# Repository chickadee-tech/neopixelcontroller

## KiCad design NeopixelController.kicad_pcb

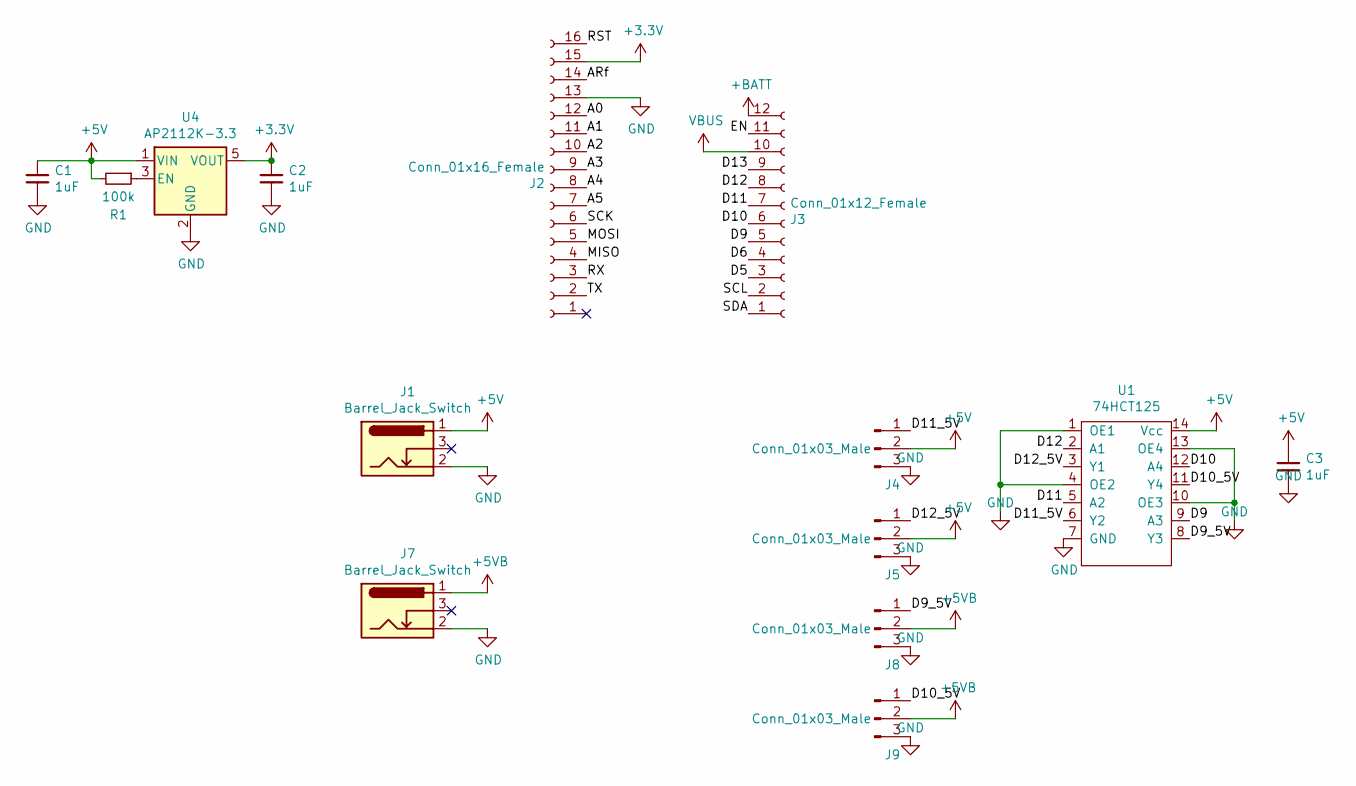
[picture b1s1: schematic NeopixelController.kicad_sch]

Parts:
C1, C2, C3: 1uF; C_0603_1608Metric_Pad1.05x0.95mm_HandSolder
J1, J7: Barrel_Jack_Switch; BarrelJack_CUI_PJ-102AH_Horizontal
J2: Conn_01x16_Female; PinSocket_1x16_P2.54mm_Vertical
J3: Conn_01x12_Female; PinSocket_1x12_P2.54mm_Vertical
J4, J5, J8, J9: Conn_01x03_Male; JST_PH_S3B-PH-K_1x03_P2.00mm_Horizontal
R1: 100k; R_0603_1608Metric_Pad1.05x0.95mm_HandSolder
U1: 74HCT125; TSSOP-14_4.4x5mm_P0.65mm
U4: AP2112K-3.3; SOT-23-5

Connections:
+3.3V: C2.1, J2.15, U4.5 (VOUT)
+5V: C1.1, C3.1, J1.1, J4.2, J5.2, R1.2, U1.14 (Vcc), U4.1 (VIN)
+5VB: J7.1, J8.2, J9.2
+BATT: J3.12
/A0: J2.12
/A1: J2.11
/A2: J2.10
/A3: J2.9
/A4: J2.8
/A5: J2.7
/ARf: J2.14
/D5: J3.3
/D6: J3.4
/D9: J3.5, U1.9 (A3)
/D9_5V: J8.1, U1.8 (Y3)
/D10: J3.6, U1.12 (A4)
/D10_5V: J9.1, U1.11 (Y4)
/D11: J3.7, U1.5 (A2)
/D11_5V: J4.1, U1.6 (Y2)
/D12: J3.8, U1.2 (A1)
/D12_5V: J5.1, U1.3 (Y1)
/D13: J3.9
/EN: J3.11
/MISO: J2.4
/MOSI: J2.5
/RST: J2.16
/RX: J2.3
/SCK: J2.6
/SCL: J3.2
/SDA: J3.1
/TX: J2.2
GND: C1.2, C2.2, C3.2, J1.2, J2.13, J4.3, J5.3, J7.2, J8.3, J9.3, U1.1 (OE1), U1.4 (OE2), U1.7 (GND), U1.10 (OE3), U1.13 (OE4), U4.2 (GND)
unnamed: R1.1, U4.3 (EN)
VBUS: J3.10

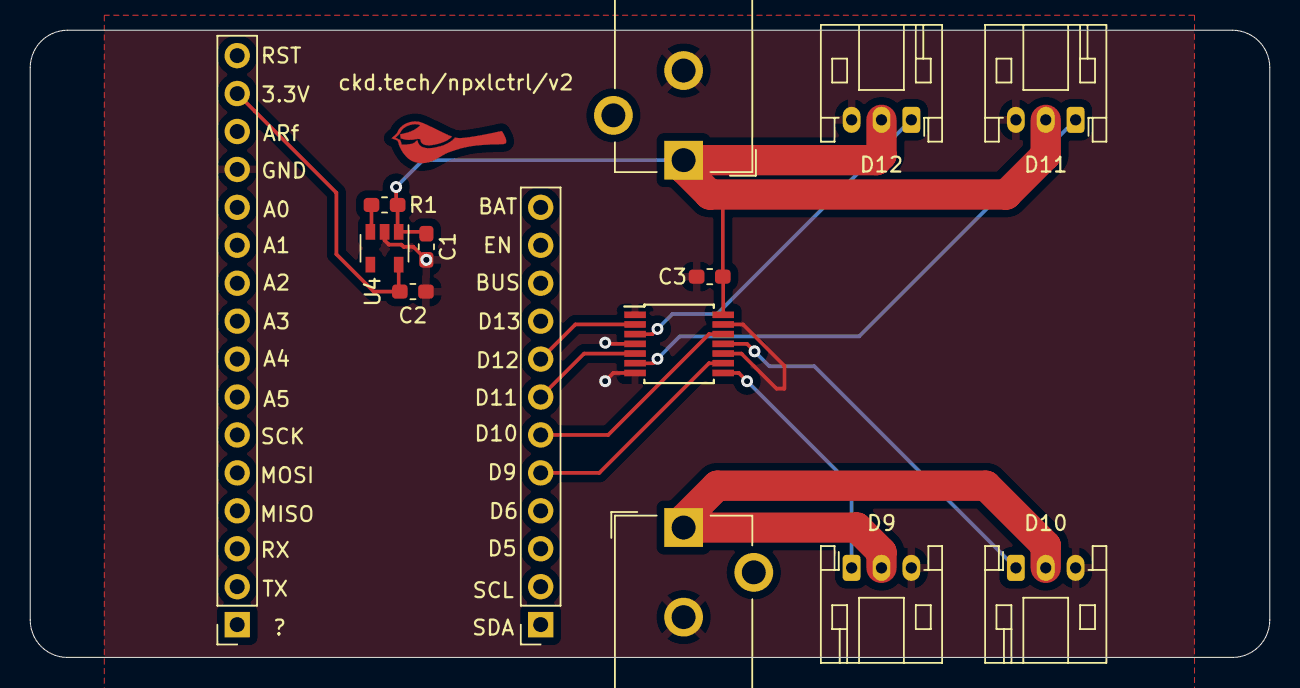
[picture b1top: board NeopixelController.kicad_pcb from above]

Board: 2 copper layers, 83.0 x 42.0 mm, 14 parts (0 on the bottom side), 13 nets.

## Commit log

2021-02-10 initial version
2025-10-24 prl and pro files
2025-10-24 V2 with four outputs
